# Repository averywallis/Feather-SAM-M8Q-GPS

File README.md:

# Feather-SAM-M8Q-GPS
 KiCad files for a SAM-M8Q GPS Featherwing

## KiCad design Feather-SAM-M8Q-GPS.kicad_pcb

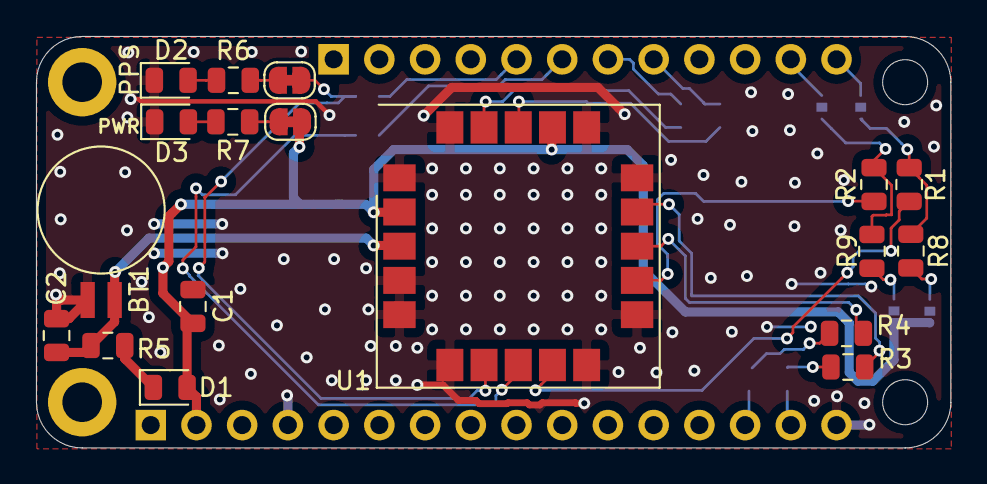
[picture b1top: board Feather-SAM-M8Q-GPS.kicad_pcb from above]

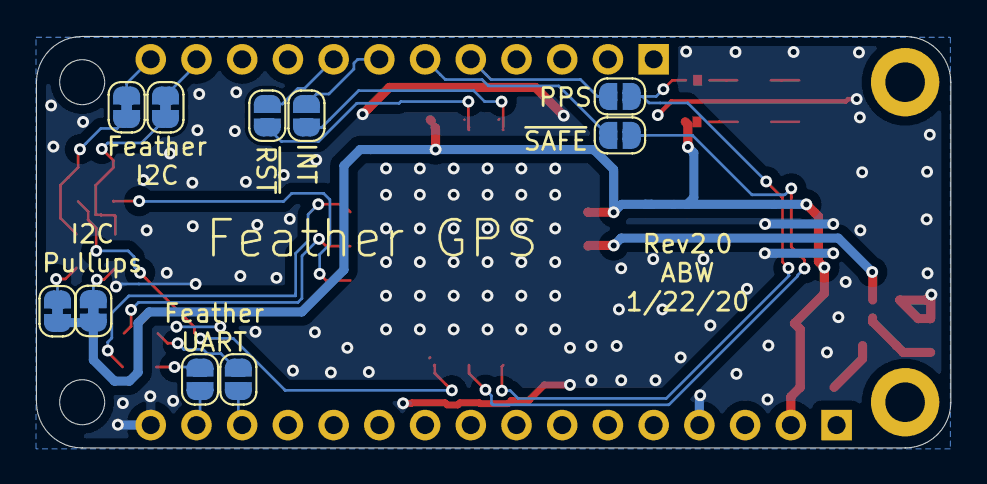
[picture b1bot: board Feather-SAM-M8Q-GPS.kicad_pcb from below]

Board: 2 copper layers, 50.8 x 22.9 mm, 28 parts (10 on the bottom side), 22 nets.

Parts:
BT1: BatteryHolder_Seiko_MS621F
C1, C2: 1.0uF; C_0805_2012Metric
D1: D_Schottky; D_0805_2012Metric
D2: YELLOW; LED_0805_2012Metric
D3: RED; LED_0805_2012Metric
JP1, JP2, JP3, JP6, JP7, JP8: SolderJumper-2_P1.3mm_Bridged_RoundedPad1.0x1.5mm
JP4, JP5, JP9, JP10, JP11, JP12: SolderJumper-2_P1.3mm_Open_RoundedPad1.0x1.5mm
R1, R2: 22; R_0805_2012Metric
R3, R4: 470; R_0805_2012Metric
R5: 3.3k; R_0805_2012Metric
R6, R7: 1k; R_0805_2012Metric
R8, R9: 2.2k; R_0805_2012Metric
U1: ublox_SAM-M8Q

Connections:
+3V3: C1.1, D1.2, JP2.1, JP3.2, JP6.2, U1.2, U1.17
/BACKUP: BT1.1, C2.1, R5.1, U1.3
/INT: JP10.2, U1.19
/PPS: JP1.1, JP12.2, U1.7
/RX: JP4.1, R3.1
/TX: JP5.1, R4.1
/~RESET: JP11.2, U1.18
/~SAFE: JP9.1, U1.8
GND: BT1.2, C1.2, C2.2, D2.1, D3.1, U1.1, U1.4, U1.5, U1.6, U1.10, U1.11, U1.15, U1.16, U1.20
unnamed: D1.1, R5.2
unnamed: D2.2, R6.1
unnamed: D3.2, R7.1
unnamed: JP1.2, R6.2
unnamed: JP2.2, R7.2
unnamed: JP3.1, R8.1
unnamed: JP6.1, R9.1
unnamed: JP7.1, R1.1, R8.2
unnamed: JP8.1, R2.1, R9.2
unnamed: R1.2, U1.9
unnamed: R2.2, U1.12
unnamed: R3.2, U1.14
unnamed: R4.2, U1.13

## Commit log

2020-01-24 Rev1.5 of SAM-M8Q GPS
2022-01-29 Create LICENSE
